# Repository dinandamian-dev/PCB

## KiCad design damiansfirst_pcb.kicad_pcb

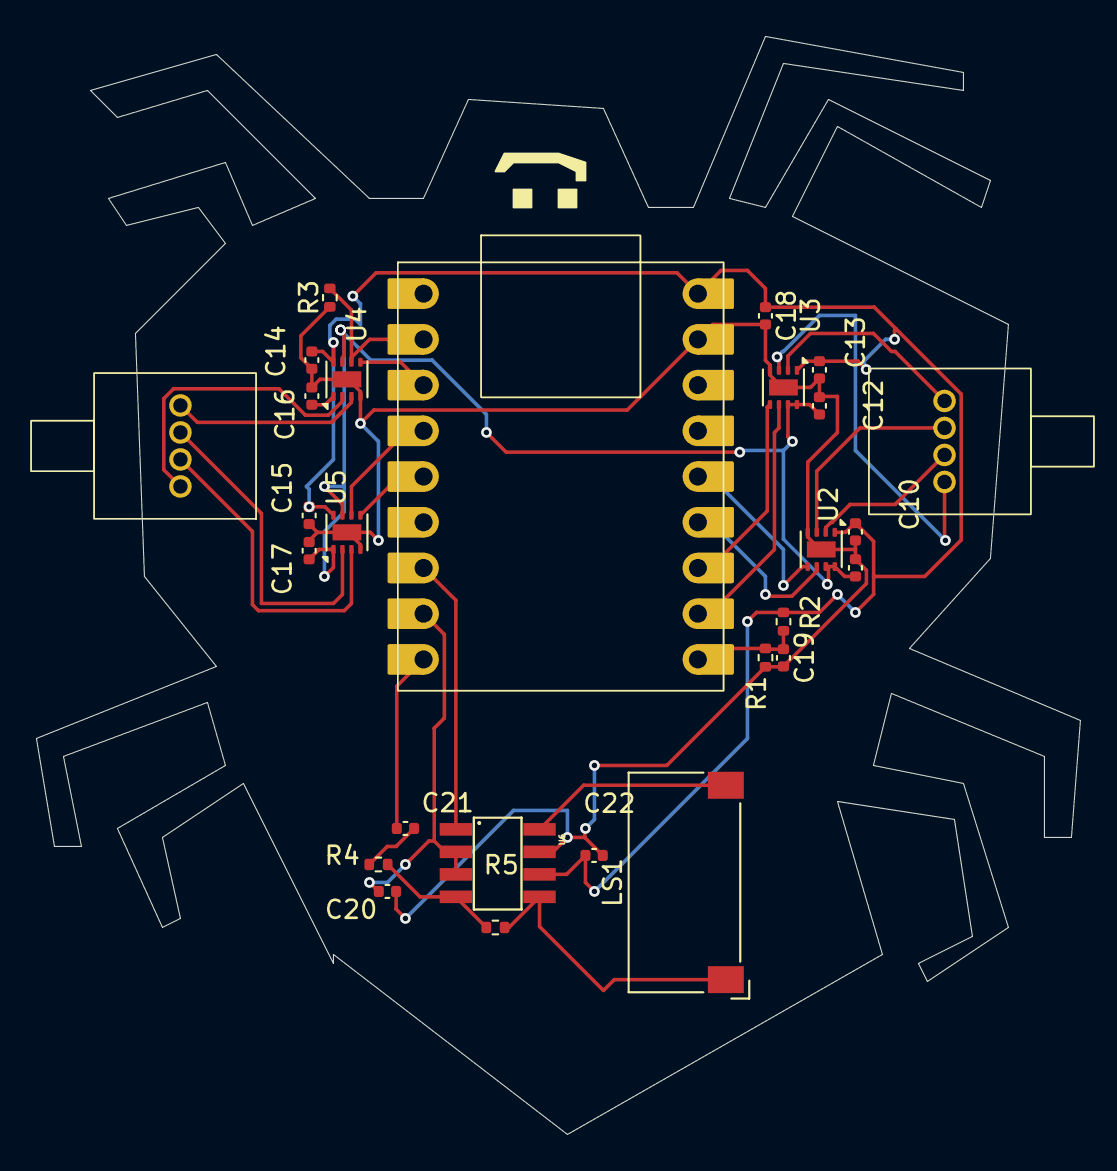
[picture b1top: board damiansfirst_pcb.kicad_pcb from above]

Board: 2 copper layers, 58.0 x 61.0 mm, 27 parts (0 on the bottom side), 28 nets.

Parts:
C10, C11, C12, C13, C14, C15, C16, C17, C19, C20, C21: 0.1uF; C_0402_1005Metric
C18, C22: 10uF; C_0402_1005Metric
J1, J2: Conn_01x04; PM08_stepper_motor
LS1: Speaker; Speaker_CUI_CMR-1206S-67
R1, R2, R3: 10k; R_0402_1005Metric
R4, R5: 20k; R_0402_1005Metric
U1: ESP32S3; ESP32-S3-SUPERMINI
U2, U3, U4, U5: DRV8837; WSON-8-1EP_2x2mm_P0.5mm_EP0.9x1.6mm
U6: NCS2211; SOIC-8

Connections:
+3.3V: C11.1, C12.1, C17.1, U2.7 (~SLEEP), U2.8 (VCC), U3.7 (~SLEEP), U3.8 (VCC), U4.7 (~SLEEP), U5.1 (VM), U5.7 (~SLEEP)
GND: C10.2, C11.2, C12.2, C13.2, C14.2, C15.2, C16.2, C17.2, C18.2, C19.2, C20.2, C22.2, R1.2, R3.1, U1.17 (GND), U2.4 (GND), U2.9 (GND), U3.4 (GND), U3.9 (GND), U4.4 (GND), U4.9 (GND), U5.4 (GND), U5.9 (GND), U6.7 (VEE)
unnamed: C21.2, R4.1
unnamed: J1.1, U3.2 (OUT1)
unnamed: J1.2, U2.3 (OUT2)
unnamed: J1.3, U2.2 (OUT1)
unnamed: J1.4, U3.3 (OUT2)
unnamed: J2.1, U4.2 (OUT1)
unnamed: J2.2, U5.3 (OUT2)
unnamed: J2.3, U5.2 (OUT1)
unnamed: J2.4, U4.3 (OUT2)
unnamed: U1.3 (GPIO1), U4.5 (IN2)
unnamed: U1.4 (GPIO2), U5.6 (IN1)
unnamed: U1.5 (GPIO3), U5.5 (IN2)
unnamed: U1.7 (GPIO5), U6.1 (EN)
unnamed: C20.1, U1.8 (GPIO6), U6.2 (BIAS), U6.3 (IN+)
unnamed: C21.1, U1.9 (GPIO7)
unnamed: C19.1, R1.1, R2.2, U1.10 (GPIO8)
unnamed: U1.11 (GPIO9), U3.6 (IN1)
unnamed: U1.12 (GPIO10), U3.5 (IN2)
unnamed: U1.13 (GPIO11), U2.6 (IN1)
unnamed: U1.14 (GPIO12), U2.5 (IN2)
unnamed: R3.2, U1.2 (RX/GPIO44), U4.6 (IN1)
unnamed: C16.1, U4.1 (VM)
unnamed: R4.2, R5.1, U6.4 (IN-)
unnamed: LS1.1, R5.2, U6.5 (OUT+)
unnamed: LS1.2, U6.8 (OUT-)
VBUS: C10.1, C13.1, C14.1, C15.1, C18.1, C22.1, R2.1, U1.18 (5V), U2.1 (VM), U3.1 (VM), U4.8 (VCC), U5.8 (VCC), U6.6 (VCC)

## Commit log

2026-04-24 first commit!
